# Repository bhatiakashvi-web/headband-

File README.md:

# AashaEye
# A head-mounted device that uses text-to-speech software to scan text and convert it directly into audio using onboard processing.
# PCB: 
#   KiCad used for making the schematic, board, and footprints. 
#   Schematic & Board visuals- https://kicanvas.org/?repo=https%3A%2F%2Fgithub.com%2Fbhatiakashvi-web%2Fheadband-%2Ftree%2Fmain
#     Images of the board and schematic:

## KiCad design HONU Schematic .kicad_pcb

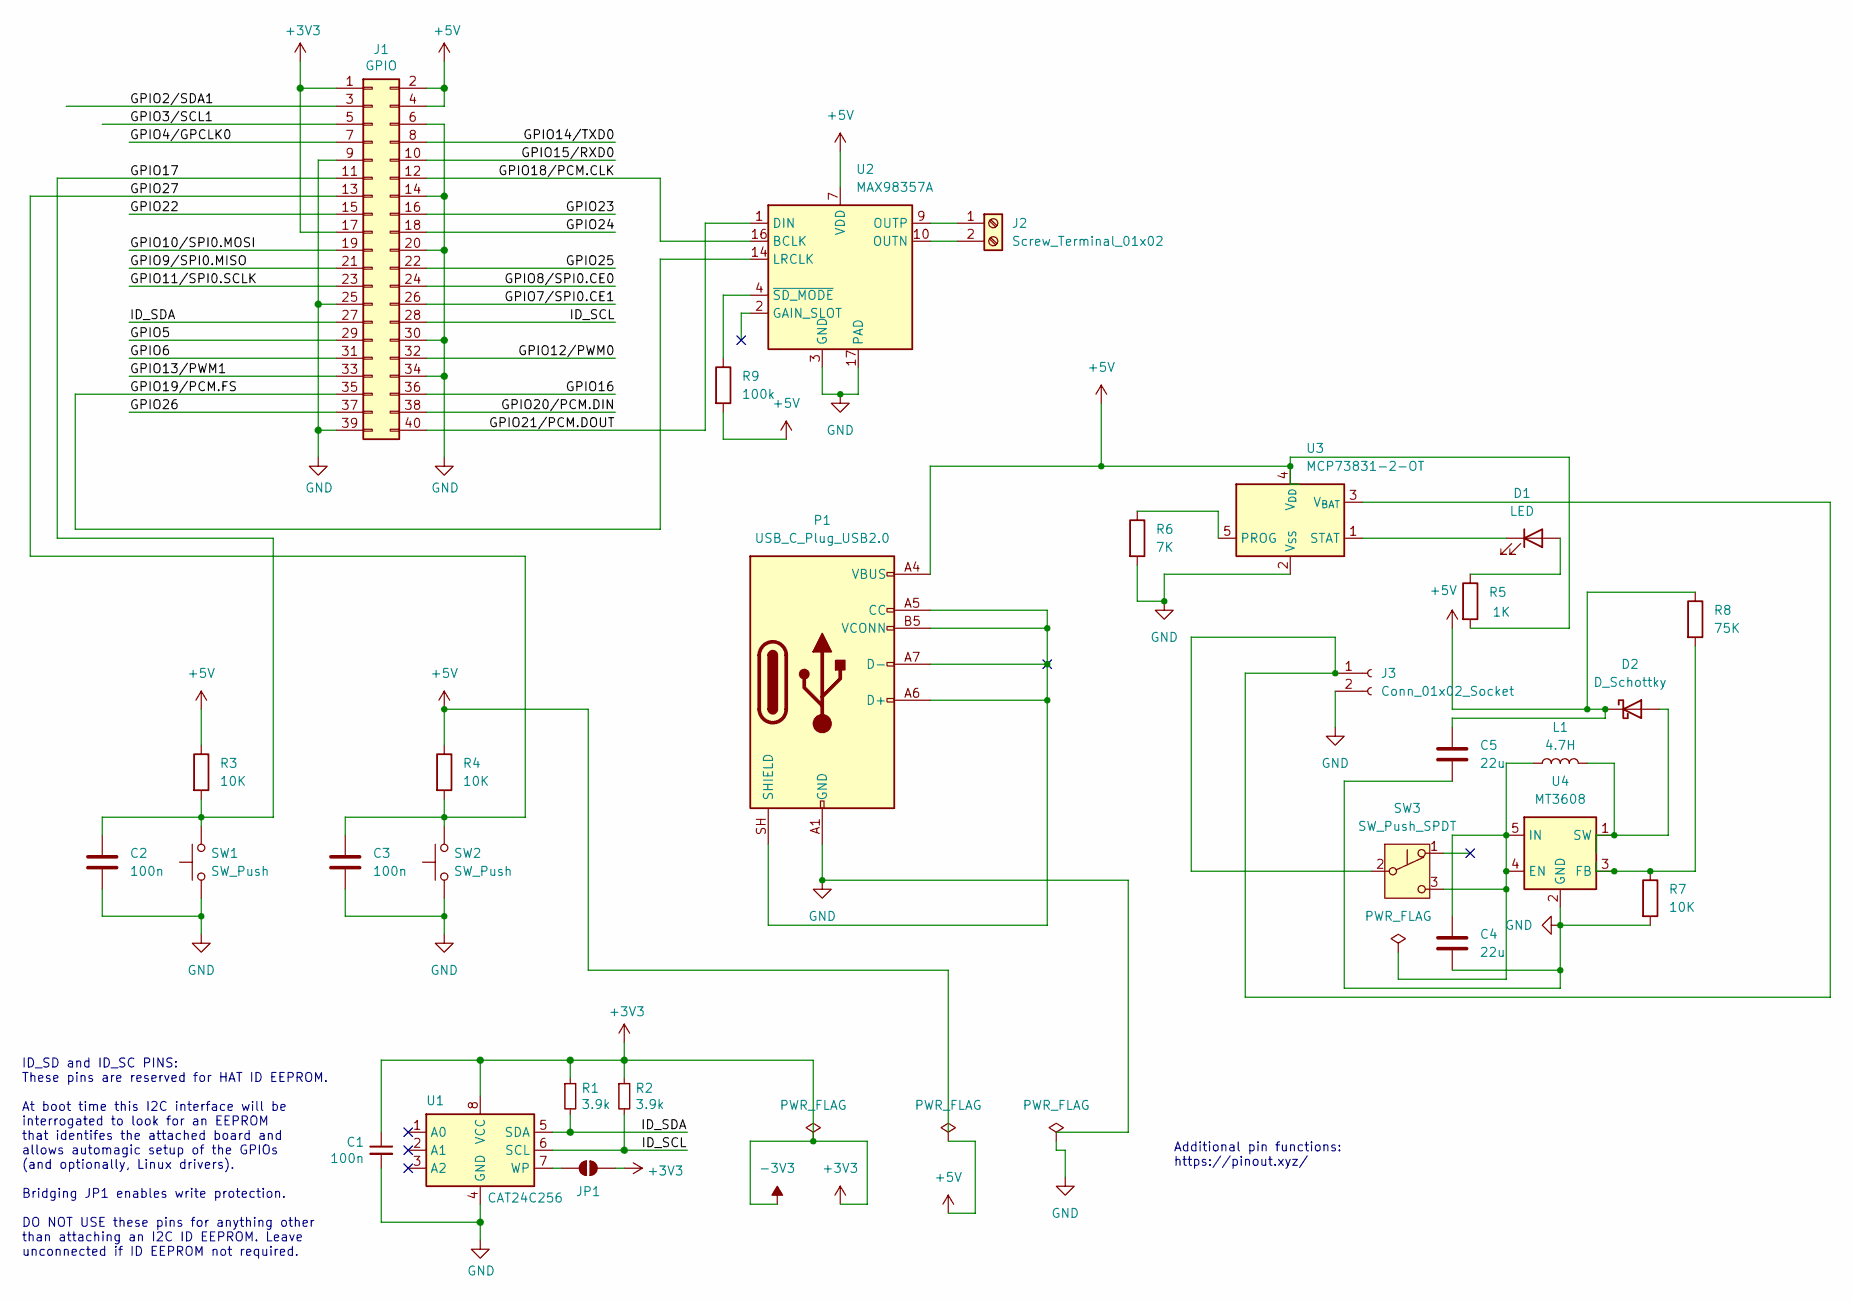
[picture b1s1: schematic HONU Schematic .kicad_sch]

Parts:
C1, C2, C3: 100n; C_0805_2012Metric
C4, C5: 22u; C_1206_3216Metric
D1: LED; LED_0805_2012Metric
D2: D_Schottky; D_SOD-123
J1: GPIO; PinSocket_2x20_P2.54mm_Vertical
J2: Screw_Terminal_01x02; TerminalBlock_Phoenix_MKDS-1,5-2-5.08_1x02_P5.08mm_Horizont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
J3: Conn_01x02_Socket; JST_PH_B2B-PH-K_1x02_P2.00mm_Vertical
JP1: ID_WP; PinHeader_2x20_P2.54mm_Vertical
L1: 4.7H; L_Bourns-SRN4018
P1: USB_C_Plug_USB2.0; USB_C_Receptacle_HRO_TYPE-C-31-M-12
R1, R2: 3.9k; R_0805_2012Metric
R3, R4, R7: 10K; R_0805_2012Metric
R5: 1K; R_0805_2012Metric
R6: 7K; R_0805_2012Metric
R8: 75K; R_0805_2012Metric
R9: 100k; R_0805_2012Metric
SW1, SW2: SW_Push; SW_PUSH_6mm_H4.3mm
SW3: SW_Push_SPDT; SW_CK_JS202011CQN_DPDT_Straight
U1: CAT24C256; SOIC-8_3.9x4.9mm_P1.27mm
U2: MAX98357A; TQFN-16-1EP_3x3mm_P0.5mm_EP1.23x1.23mm
U3: MCP73831-2-OT; SOT-23-5
U4: MT3608; SOT-23-6

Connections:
+3V3: C1.1, J1.1, J1.17, JP1.2 (B), R1.1, R2.1, U1.8 (VCC)
+5V: C5.1, D2.1 (K), J1.2, J1.4, P1.A4 (VBUS), P1.A9 (VBUS), P1.B4 (VBUS), P1.B9 (VBUS), R3.1, R4.1, R5.2, R8.1, R9.2, U2.7 (VDD), U2.8 (VDD), U3.4 (V_{DD})
/GPIO2/SDA1: J1.3
/GPIO3/SCL1: J1.5
/GPIO4/GPCLK0: J1.7
/GPIO5: J1.29
/GPIO6: J1.31
/GPIO7/SPI0.CE1: J1.26
/GPIO8/SPI0.CE0: J1.24
/GPIO9/SPI0.MISO: J1.21
/GPIO10/SPI0.MOSI: J1.19
/GPIO11/SPI0.SCLK: J1.23
/GPIO12/PWM0: J1.32
/GPIO13/PWM1: J1.33
/GPIO14/TXD0: J1.8
/GPIO15/RXD0: J1.10
/GPIO16: J1.36
/GPIO17: C2.1, J1.11, R3.2, SW1.2
/GPIO18/PCM.CLK: J1.12, U2.16 (BCLK)
/GPIO19/PCM.FS: J1.35, U2.14 (LRCLK)
/GPIO20/PCM.DIN: J1.38
/GPIO21/PCM.DOUT: J1.40, U2.1 (DIN)
/GPIO22: J1.15
/GPIO23: J1.16
/GPIO24: J1.18
/GPIO25: J1.22
/GPIO26: J1.37
/GPIO27: C3.1, J1.13, R4.2, SW2.2
/ID_SCL: J1.28, R2.2, U1.6 (SCL)
/ID_SDA: J1.27, R1.2, U1.5 (SDA)
GND: C1.2, C2.2, C3.2, C4.2, C5.2, J1.6, J1.9, J1.14, J1.20, J1.25, J1.30, J1.34, J1.39, J3.2, P1.A1 (GND), P1.A12 (GND), P1.B1 (GND), P1.B12 (GND), R6.2, R7.2, SW1.1, SW2.1, U1.4 (GND), U2.3 (GND), U2.11 (GND), U2.15 (GND), U2.17 (PAD), U3.2 (V_{SS}), U4.2 (GND)
unnamed: D1.2 (A), R5.1
unnamed: D1.1 (K), U3.1 (STAT)
unnamed: D2.2 (A), L1.2, U4.1 (SW), U4.6 (NC)
unnamed: J2.1, U2.9 (OUTP)
unnamed: J2.2, U2.10 (OUTN)
unnamed: J3.1, SW3.2 (B), U3.3 (V_{BAT})
unnamed: JP1.1 (A), U1.7 (WP)
unnamed: C4.1, L1.1, SW3.3 (C), U4.4 (EN), U4.5 (IN)
unnamed: R9.1, U2.4 (~SD_MODE)
unnamed: R6.1, U3.5 (PROG)
unnamed: R7.1, R8.2, U4.3 (FB)

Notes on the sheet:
Additional pin functions: https://pinout.xyz/
ID_SD and ID_SC PINS: These pins are reserved for HAT ID EEPROM. At boot time this I2C interface will be interrogated to look for an EEPROM that identifes the attached board and allows automagic setup of the GPIOs (and optionally, Linux drivers). Bridging JP1 enables write protection. DO NOT USE th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

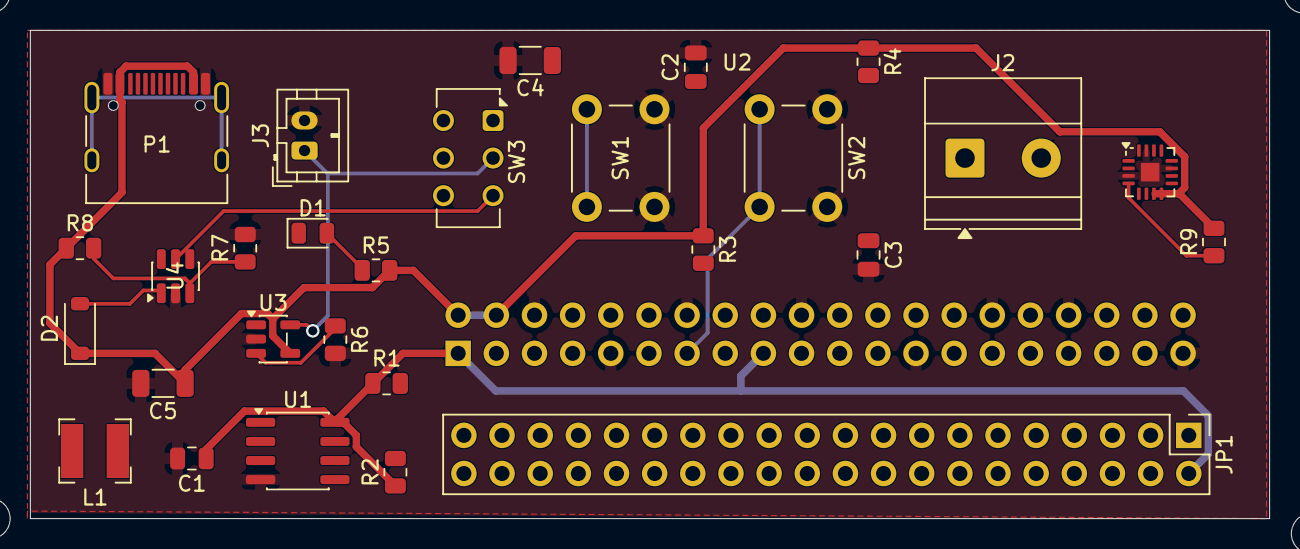
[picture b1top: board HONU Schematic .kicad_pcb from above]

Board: 2 copper layers, 82.5 x 32.5 mm, 33 parts (1 on the bottom side), 21 nets.

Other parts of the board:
MH1, MH2, MH3, MH4: MountingHole_2.7mm_M2.5

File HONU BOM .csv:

"Value","Footprint","Qty","DNP"
"100n","Capacitor_SMD:C_0805_2012Metric","3",""
"22u","Capacitor_SMD:C_1206_3216Metric","2",""
"LED","LED_SMD:LED_0805_2012Metric","1",""
"D_Schottky","Diode_SMD:D_SOD-123","1",""
"GPIO","Connector_PinSocket_2.54mm:PinSocket_2x20_P2.54mm_Vertical","1",""
"Screw_Terminal_01x02","TerminalBlock_Phoenix:TerminalBlock_Phoenix_MKDS-1,5-2-5.08_1x02_P5.08mm_Horizontal","1",""
"Conn_01x02_Socket","Connector_JST:JST_PH_B2B-PH-K_1x02_P2.00mm_Vertical","1",""
"ID_WP","Connector_PinHeader_2.54mm:PinHeader_2x20_P2.54mm_Vertical","1",""
"4.7H","Inductor_SMD:L_Bourns-SRN4018","1",""
"USB_C_Plug_USB2.0","Connector_USB:USB_C_Receptacle_HRO_TYPE-C-31-M-12","1",""
"3.9k","Resistor_SMD:R_0805_2012Metric","2",""
"10K","Resistor_SMD:R_0805_2012Metric","3",""
"1K","Resistor_SMD:R_0805_2012Metric","1",""
"7K","Resistor_SMD:R_0805_2012Metric","1",""
"75K","Resistor_SMD:R_0805_2012Metric","1",""
"100k","Resistor_SMD:R_0805_2012Metric","1",""
"SW_Push","Button_Switch_THT:SW_PUSH_6mm_H4.3mm","2",""
"SW_Push_SPDT","Button_Switch_THT:SW_CK_JS202011CQN_DPDT_Straight","1",""
"CAT24C256","Package_SO:SOIC-8_3.9x4.9mm_P1.27mm","1",""
"MAX98357A","Package_DFN_QFN:TQFN-16-1EP_3x3mm_P0.5mm_EP1.23x1.23mm","1",""
"MCP73831-2-OT","Package_TO_SOT_SMD:SOT-23-5","1",""
"MT3608","Package_TO_SOT_SMD:SOT-23-6","1",""
